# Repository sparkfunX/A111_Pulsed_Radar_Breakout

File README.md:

SparkX A111 Pulsed Radar Breakout
========================================

[*SparkX  A111 Pulsed Radar Breakout (SPX-14811)*](https://www.sparkfun.com/products/14811)

Does your project require high-precision, cutting-edge distance measurement? Or maybe speed-, motion-, or gesture-sensing? We’re not talking about simple ultrasonic, or even infrared, sensors here, but 60GHz radar! Well say hello to our tiny, pulsed-radar friend: the Acconeer A111.

The A111 is a single-chip solution for pulsed coherent radar (PCR). It comes complete with integrated antennae and an SPI interface capable of clock speeds of up to 50MHz. The A111’s primary use case is distance-sensing, but it also supports applications in gesture-, motion-, material-, and speed-detection. It can see objects at distances of up to two meters.

Our breakout board for the A111 includes a 1.8V regulator, voltage-level translation between 1.8V and either 3.3V or 5V, and, of course, it breaks out all pins of the pulsed radar sensor to both 0.1-inch and Raspberry Pi-friendly headers.

The breakout board is primarily **designed to interface directly with a Raspberry Pi** – Acconeer’s SDK currently only supports ARMv7’s (e.g. a Pi) and ARM Cortex-M4’s. Check out our <a href="https://learn.sparkfun.com/tutorials/using-the-a111-pulsed-radar-sensor-with-a-raspberry-pi">Using the A111 Pulsed Radar Breakout tutorial</a>, which explains how to use the sensor with a Raspberry Pi.

**Update!**
The tutorial describes the process for an older version of the
Acconeer SDK that is nolonger available.

New installation instructions:
1. Download and unpack Acconeer SDK 1.7.0 for XC111
2. Copy the `user_source` and `user_rule` folders from this repository to the root of the unpacked
   SDK (folders `lib`, `source` and `rule` should be siblings to the
   `user_rule`and `user_source`)

SparkFun labored with love to create this code. Feel like supporting open source hardware? 
Buy a [breakout board](https://www.sparkfun.com/products/14811) from SparkFun!

Repository Contents
-------------------

* **/Documents** - Datasheets
* **/Hardware** - Eagle design files (.brd, .sch)
* **/Software** - Example code and board-definition files to be added to the Acconeer ARMv7 SDK

License Information
-------------------

This product is _**open source**_! 

If you have any questions or concerns on licensing, please contact techsupport@sparkfun.com.

Please use, reuse, and modify these files as you see fit. Please maintain attribution to SparkFun Electronics and release any derivative under the same license.

Distributed as-is; no warranty is given.

- Your friends at SparkFun.

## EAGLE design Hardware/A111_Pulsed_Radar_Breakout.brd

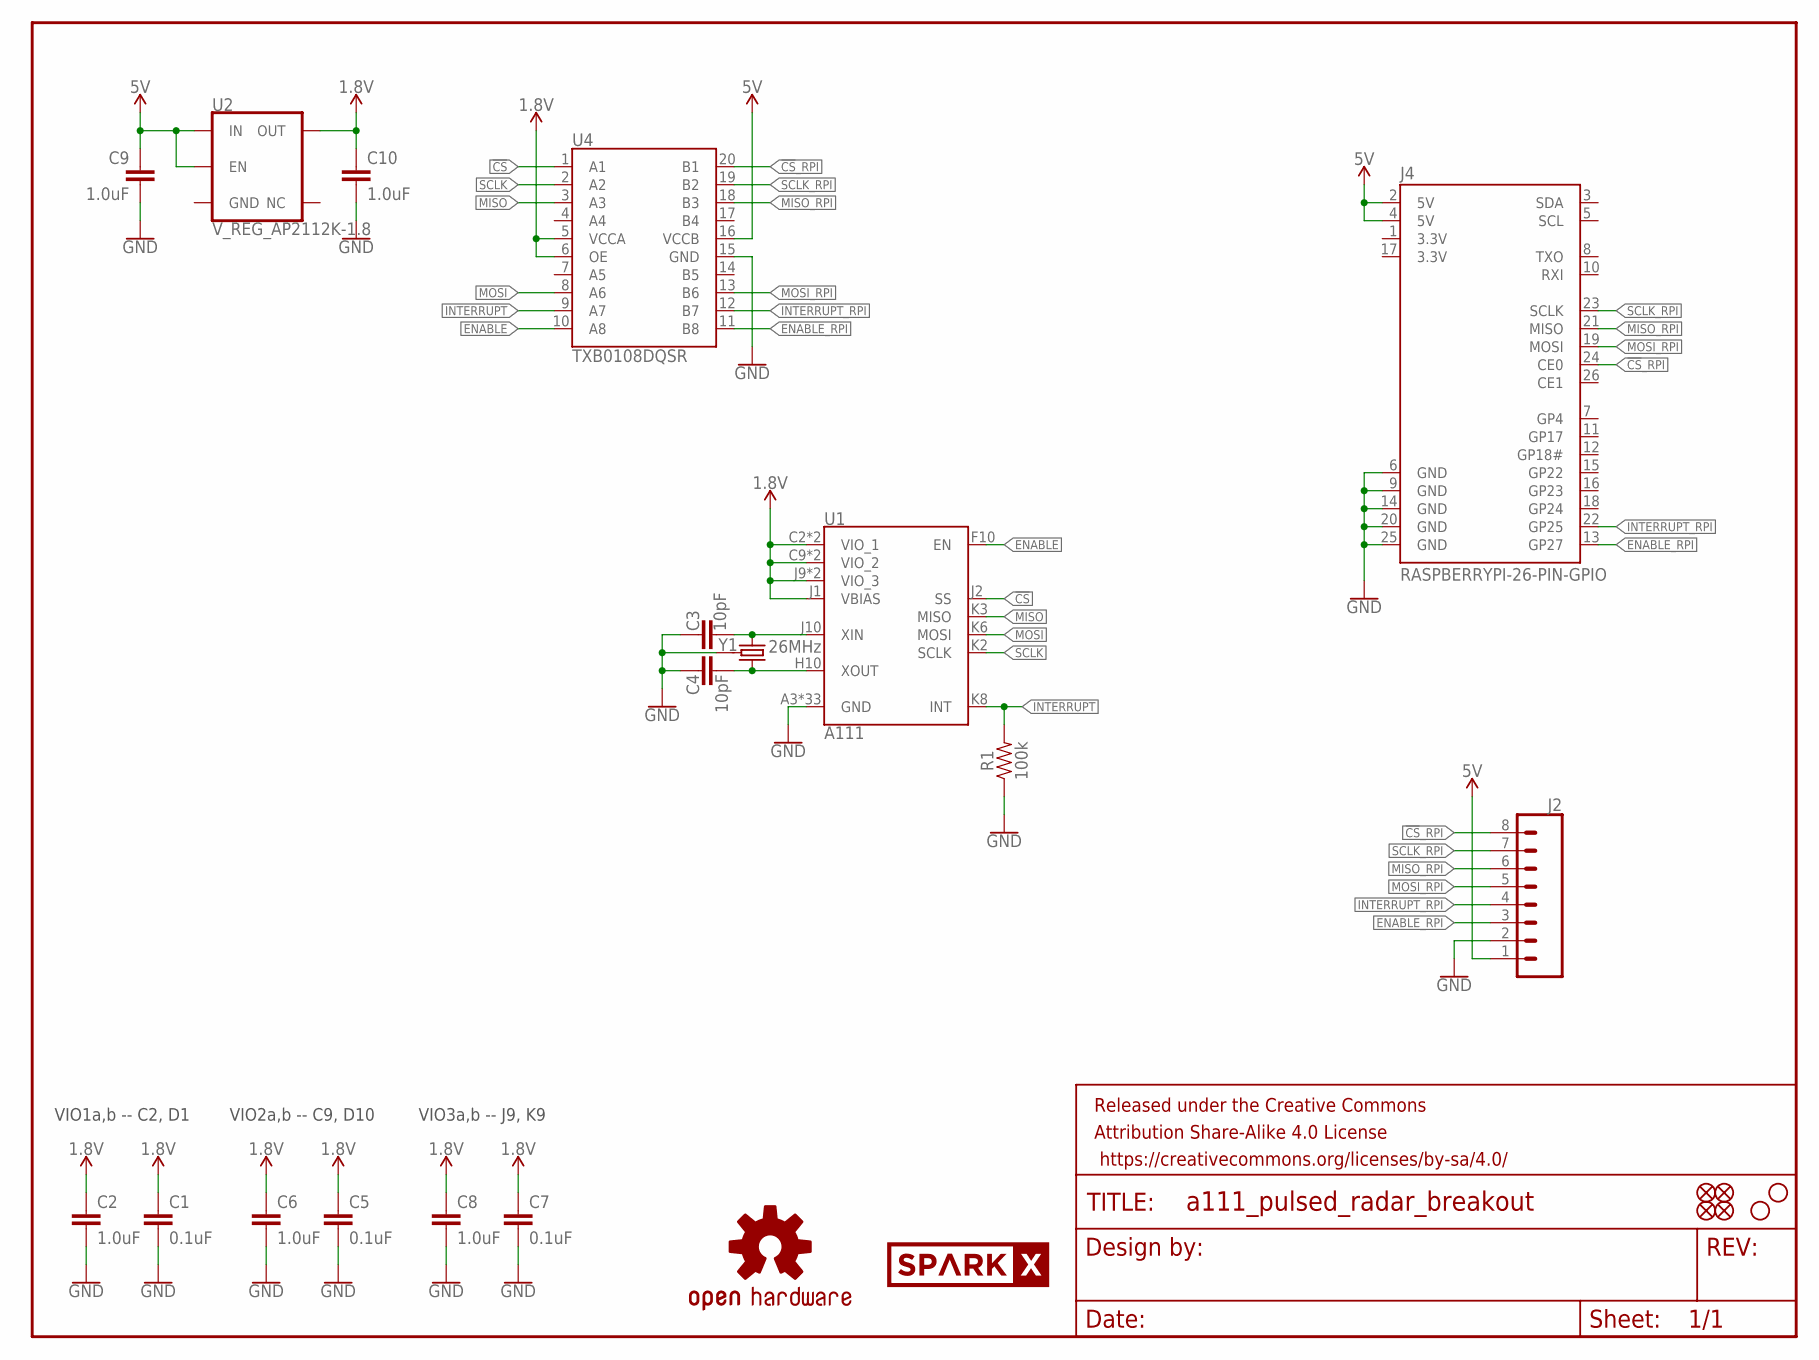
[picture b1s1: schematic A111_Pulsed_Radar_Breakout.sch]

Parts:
C1, C5, C7: 0.1uF; 0603
C2, C6, C8, C9, C10: 1.0uF; 0603
C3, C4: 10pF; 0603
FD1, FD2, FD3, FD4: FIDUCIALUFIDUCIAL; FIDUCIAL-MICRO
FRAME1: FRAME-LETTER; CREATIVE_COMMONS
H1, H2: STAND-OFF
J2: CONN_08NO_SILK_FEMALE_PTH; 1X08_NO_SILK
J4: RASPBERRYPI-26-PIN-GPIO; 2X13
LOGO1: SPARKX-LOGO5; SPARKX-LARGE
LOGO2: OSHW-LOGOM; OSHW-LOGO-M
R1: 100k; 0603
U1: A111
U2: V_REG_AP2112K-1.8; SOT23-5
U4: TXB0108DQSR; UFDFN-20
Y1: 26MHz; CRYSTAL-SMD-3.2X2.5MM

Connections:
1.8V: C1.1, C2.1, C5.1, C6.1, C7.1, C8.1, C10.1, U1.C2 (VIO_1), U1.C9 (VIO_2), U1.D1 (VIO_1), U1.D10 (VIO_2), U1.J1 (VBIAS), U1.J9 (VIO_3), U1.K9 (VIO_3), U2.5 (OUT), U4.5 (VCCA), U4.6 (OE)
5V: C9.1, J2.1, J4.2 (5V), J4.4 (5V), U2.1 (IN), U2.3 (EN), U4.16 (VCCB)
!CS!: U1.J2 (SS), U4.1 (A1)
!CS!_RPI: J2.8, J4.24 (CE0), U4.20 (B1)
ENABLE: U1.F10 (EN), U4.10 (A8)
ENABLE_RPI: J2.3, J4.13 (GP27), U4.11 (B8)
GND: C1.2, C2.2, C3.2, C4.1, C5.2, C6.2, C7.2, C8.2, C9.2, C10.2, J2.2, J4.6 (GND), J4.9 (GND), J4.14 (GND), J4.20 (GND), J4.25 (GND), R1.1, U1.A3 (GND), U1.A4 (GND), U1.A5 (GND), U1.A6 (GND), U1.A7 (GND), U1.A8 (GND), U1.A9 (GND), U1.B2 (GND), U1.B9 (GND), U1.B10 (GND), U1.C1 (GND), U1.C10 (GND), U1.D2 (GND), U1.D9 (GND), U1.E1 (GND), U1.E2 (GND), U1.E9 (GND), U1.E10 (GND), U1.F1 (GND), U1.F2 (GND), U1.F9 (GND), U1.G1 (GND), U1.G10 (GND), U1.H1 (GND), U1.H2 (GND), U1.H9 (GND), U1.J3 (GND), U1.J5 (GND), U1.J6 (GND), U1.J8 (GND), U1.K4 (GND), U1.K5 (GND), U1.K7 (GND), U4.15 (GND), Y1.2 (3), Y1.4 (3)
INTERRUPT: R1.2, U1.K8 (INT), U4.9 (A7)
INTERRUPT_RPI: J2.4, J4.22 (GP25), U4.12 (B7)
MISO: U1.K3 (MISO), U4.3 (A3)
MISO_RPI: J2.6, J4.21 (MISO), U4.18 (B3)
MOSI: U1.K6 (MOSI), U4.8 (A6)
MOSI_RPI: J2.5, J4.19 (MOSI), U4.13 (B6)
unnamed: C3.1, U1.J10 (XIN), Y1.1
unnamed: C4.2, U1.H10 (XOUT), Y1.3 (2)
SCLK: U1.K2 (SCLK), U4.2 (A2)
SCLK_RPI: J2.7, J4.23 (SCLK), U4.19 (B2)

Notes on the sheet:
VIO1a,b -- C2, D1
VIO2a,b -- C9, D10
VIO3a,b -- J9, K9

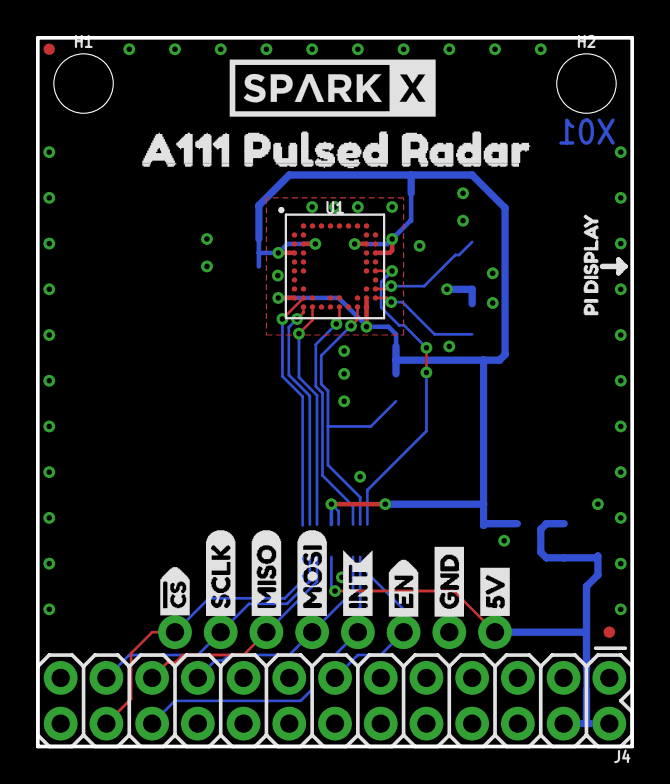
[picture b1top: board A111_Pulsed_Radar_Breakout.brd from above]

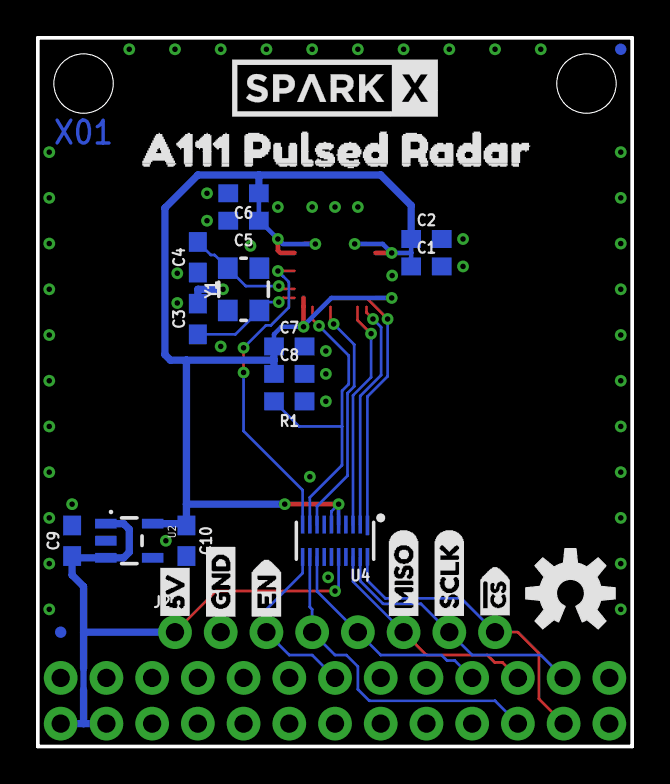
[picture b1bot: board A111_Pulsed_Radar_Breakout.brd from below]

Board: 2 copper layers, 33.0 x 39.4 mm, 44 parts (26 on the bottom side), 17 nets.

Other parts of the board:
LOGO3: SPARKX-LOGO5; SPARKX-LARGE
U$1, U$9: A111_PULSED_RADAR9
U$2, U$10: SCLK3
U$3, U$11: MISO4
U$4: MOSI5
U$5: INT8
U$6, U$18: EN9
U$7, U$15: GND0
U$8, U$16: 5V1
U$12: PI_DISPLAY9
U$13, U$17: #CS9

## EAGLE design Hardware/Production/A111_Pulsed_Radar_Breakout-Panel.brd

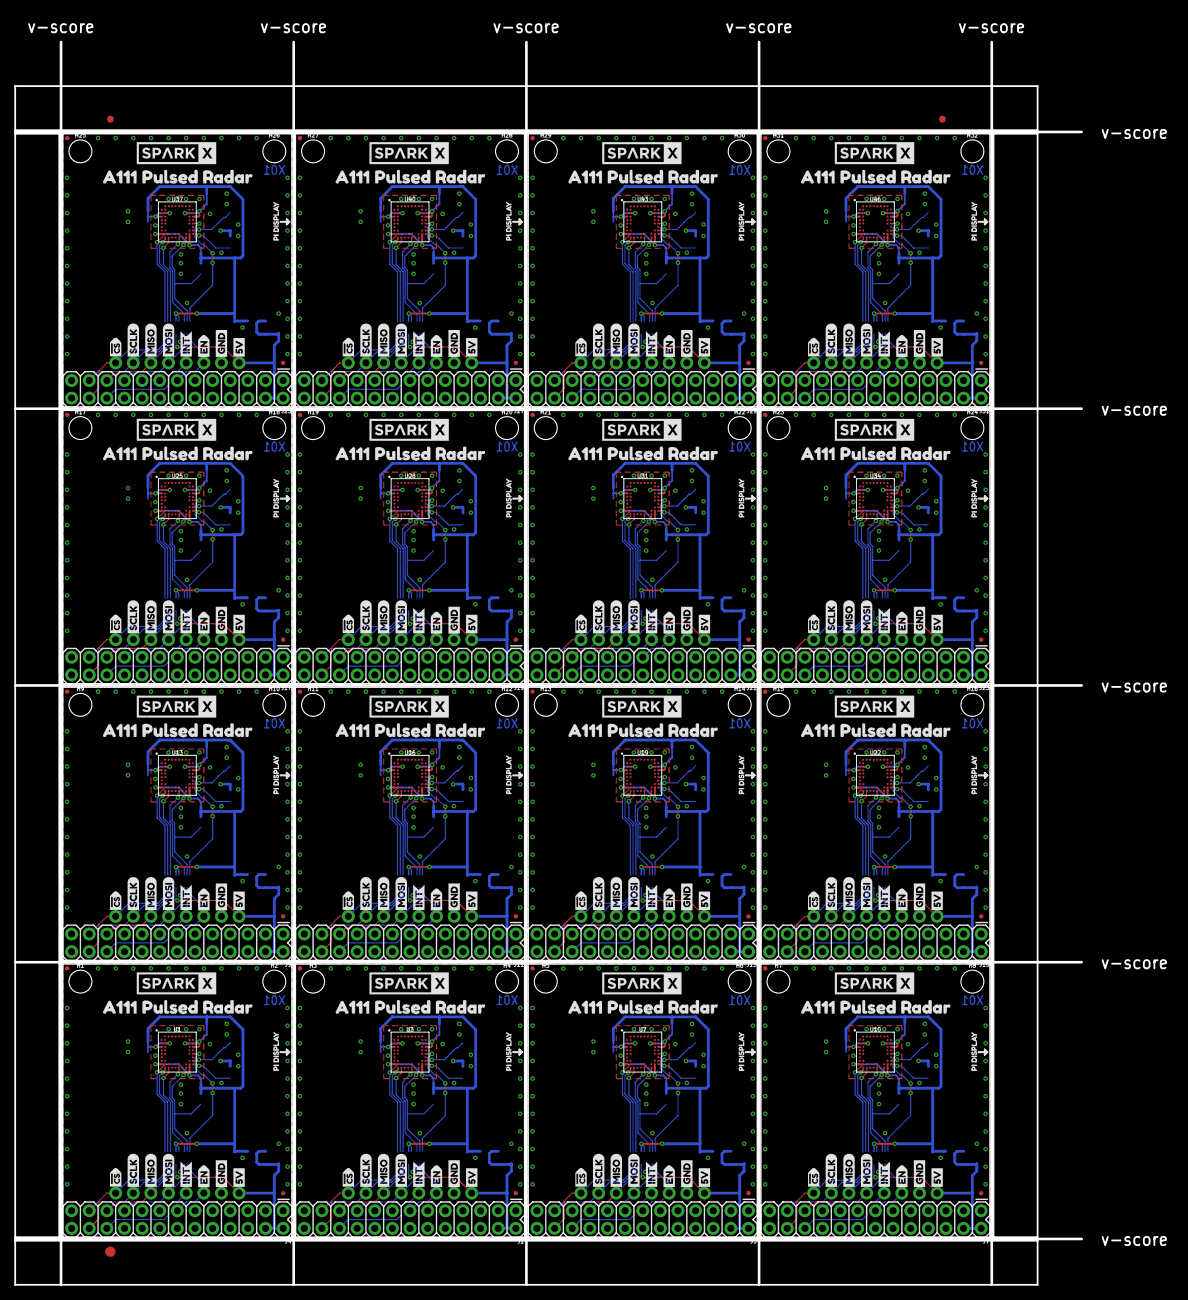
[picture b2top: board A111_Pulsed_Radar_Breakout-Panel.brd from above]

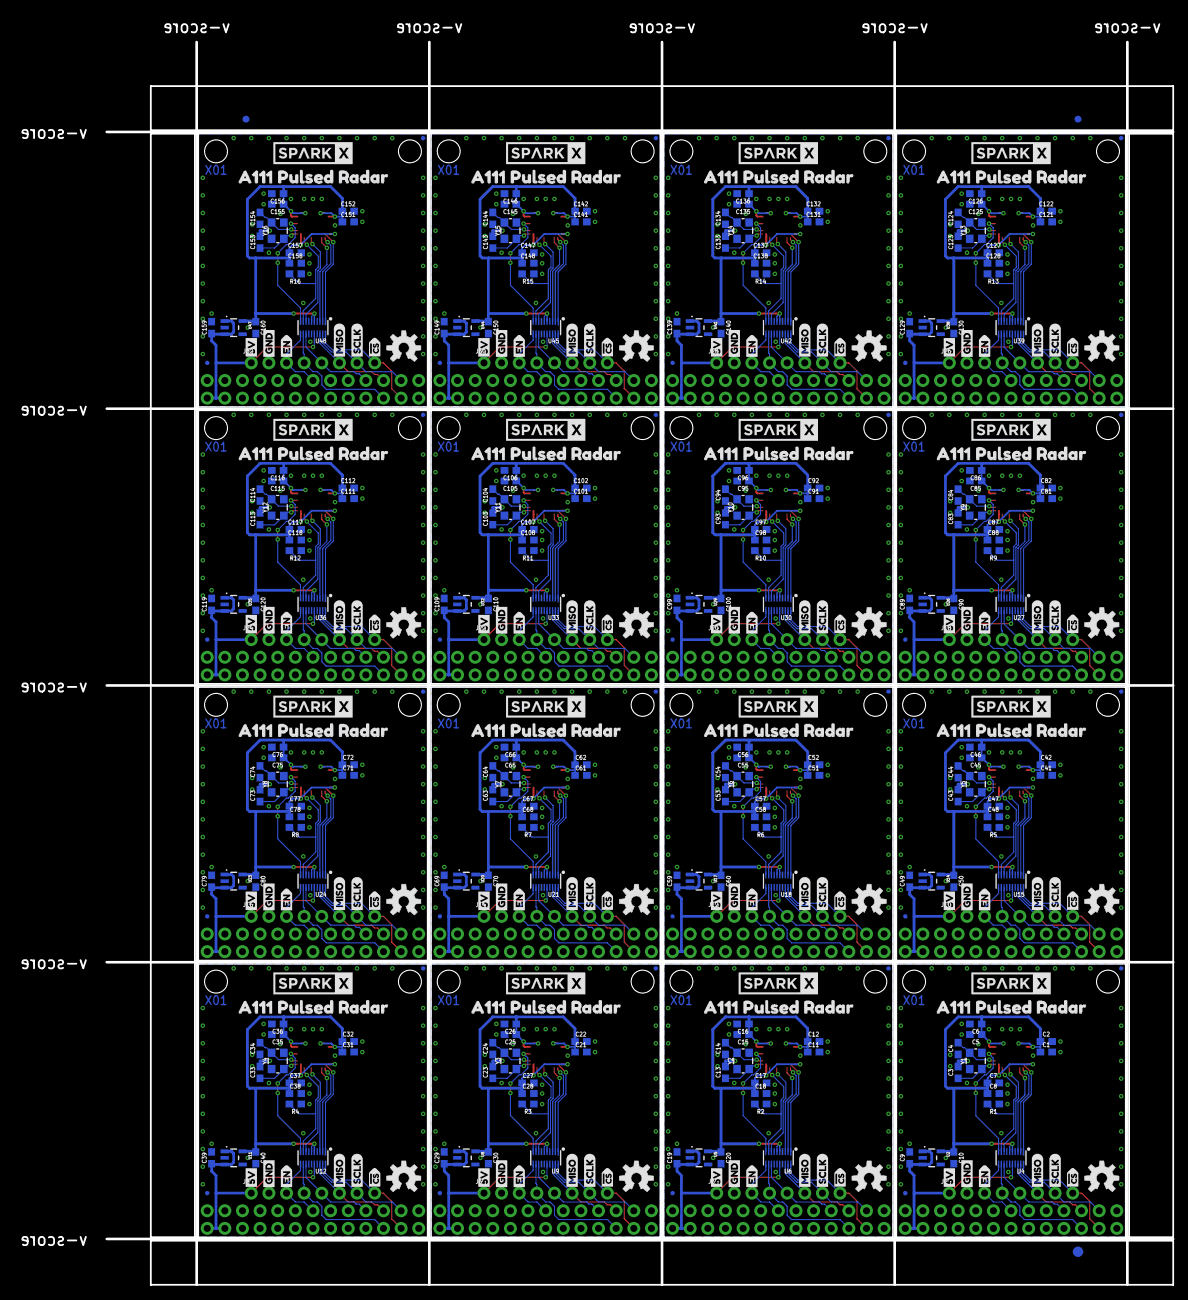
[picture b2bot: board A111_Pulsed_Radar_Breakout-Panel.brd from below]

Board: 2 copper layers, 166.9 x 182.9 mm, 694 parts (419 on the bottom side), 272 nets.

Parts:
C1, C5, C7, C11, C15, C17, C21, C25, C27, C31, C35, C37, C41, C45, C47, C51, C55, C57, C61, C65, C67, C71, C75, C77, C81, C85, C87, C91, C95, C97, C101, C105, C107, C111, C115, C117, C121, C125, C127, C131, C135, C137, C141, C145, C147, C151, C155, C157: 0.1uF; 0603
C2, C6, C8, C9, C10, C12, C16, C18, C19, C20, C22, C26, C28, C29, C30, C32, C36, C38, C39, C40, C42, C46, C48, C49, C50, C52, C56, C58, C59, C60, C62, C66, C68, C69, C70, C72, C76, C78, C79, C80, C82, C86, C88, C89, C90, C92, C96, C98, C99, C100, C102, C106, C108, C109, C110, C112, C116, C118, C119, C120, C122, C126, C128, C129, C130, C132, C136, C138, C139, C140, C142, C146, C148, C149, C150, C152, C156, C158, C159, C160: 1.0uF; 0603
C3, C4, C13, C14, C23, C24, C33, C34, C43, C44, C53, C54, C63, C64, C73, C74, C83, C84, C93, C94, C103, C104, C113, C114, C123, C124, C133, C134, C143, C144, C153, C154: 10pF; 0603
E$1, E$2, E$3, E$4: FIDUCIAL-1X2
E$5, E$6: FIDUCIAL-1.5X3
FD1, FD2, FD3, FD4, FD5, FD6, FD7, FD8, FD9, FD10, FD11, FD12, FD13, FD14, FD15, FD16, FD17, FD18, FD19, FD20, FD21, FD22, FD23, FD24, FD25, FD26, FD27, FD28, FD29, FD30, FD31, FD32, FD33, FD34, FD35, FD36, FD37, FD38, FD39, FD40, FD41, FD42, FD43, FD44, FD45, FD46, FD47, FD48, FD49, FD50, FD51, FD52, FD53, FD54, FD55, FD56, FD57, FD58, FD59, FD60, FD61, FD62, FD63, FD64: FIDUCIALUFIDUCIAL; FIDUCIAL-MICRO
H1, H2, H3, H4, H5, H6, H7, H8, H9, H10, H11, H12, H13, H14, H15, H16, H17, H18, H19, H20, H21, H22, H23, H24, H25, H26, H27, H28, H29, H30, H31, H32: STAND-OFF
J1, J4, J5, J7, J9, J11, J13, J15, J17, J19, J21, J23, J25, J27, J29, J31: RASPBERRYPI-26-PIN-GPIO; 2X13
J2, J3, J6, J8, J10, J12, J14, J16, J18, J20, J22, J24, J26, J28, J30, J32: 1X08_NO_SILK
LOGO1, LOGO3, LOGO4, LOGO6, LOGO7, LOGO9, LOGO10, LOGO12, LOGO13, LOGO15, LOGO16, LOGO18, LOGO19, LOGO21, LOGO22, LOGO24, LOGO25, LOGO27, LOGO28, LOGO30, LOGO31, LOGO33, LOGO34, LOGO36, LOGO37, LOGO39, LOGO40, LOGO42, LOGO43, LOGO45, LOGO46, LOGO48: SPARKX-LOGO5; SPARKX-LARGE
LOGO2, LOGO5, LOGO8, LOGO11, LOGO14, LOGO17, LOGO20, LOGO23, LOGO26, LOGO29, LOGO32, LOGO35, LOGO38, LOGO41, LOGO44, LOGO47: OSHW-LOGOM; OSHW-LOGO-M
R1, R2, R3, R4, R5, R6, R7, R8, R9, R10, R11, R12, R13, R14, R15, R16: 100k; 0603
U1, U3, U7, U10, U13, U16, U19, U22, U25, U28, U31, U34, U37, U40, U43, U46: A111
U2, U5, U8, U11, U14, U17, U20, U23, U26, U29, U32, U35, U38, U41, U44, U47: V_REG_AP2112K-1.8; SOT23-5
U4, U6, U9, U12, U15, U18, U21, U24, U27, U30, U33, U36, U39, U42, U45, U48: TXB0108DQSR; UFDFN-20
U$1, U$9, U$29, U$30, U$46, U$47, U$63, U$64, U$80, U$81, U$97, U$98, U$114, U$115, U$131, U$132, U$148, U$149, U$165, U$166, U$182, U$183, U$199, U$200, U$216, U$217, U$233, U$234, U$250, U$251, U$267, U$268: A111_PULSED_RADAR9
U$2, U$10, U$14, U$24, U$35, U$41, U$52, U$58, U$69, U$75, U$86, U$92, U$103, U$109, U$120, U$126, U$137, U$143, U$154, U$160, U$171, U$177, U$188, U$194, U$205, U$211, U$222, U$228, U$239, U$245, U$256, U$262: SCLK3
U$3, U$11, U$19, U$25, U$36, U$42, U$53, U$59, U$70, U$76, U$87, U$93, U$104, U$110, U$121, U$127, U$138, U$144, U$155, U$161, U$172, U$178, U$189, U$195, U$206, U$212, U$223, U$229, U$240, U$246, U$257, U$263: MISO4
U$4, U$20, U$37, U$54, U$71, U$88, U$105, U$122, U$139, U$156, U$173, U$190, U$207, U$224, U$241, U$258: MOSI5
U$5, U$21, U$38, U$55, U$72, U$89, U$106, U$123, U$140, U$157, U$174, U$191, U$208, U$225, U$242, U$259: INT8
U$6, U$18, U$33, U$34, U$50, U$51, U$67, U$68, U$84, U$85, U$101, U$102, U$118, U$119, U$135, U$136, U$152, U$153, U$169, U$170, U$186, U$187, U$203, U$204, U$220, U$221, U$237, U$238, U$254, U$255, U$271, U$272: EN9
U$7, U$15, U$22, U$26, U$39, U$43, U$56, U$60, U$73, U$77, U$90, U$94, U$107, U$111, U$124, U$128, U$141, U$145, U$158, U$162, U$175, U$179, U$192, U$196, U$209, U$213, U$226, U$230, U$243, U$247, U$260, U$264: GND0
U$8, U$16, U$23, U$27, U$40, U$44, U$57, U$61, U$74, U$78, U$91, U$95, U$108, U$112, U$125, U$129, U$142, U$146, U$159, U$163, U$176, U$180, U$193, U$197, U$210, U$214, U$227, U$231, U$244, U$248, U$261, U$265: 5V1
U$12, U$31, U$48, U$65, U$82, U$99, U$116, U$133, U$150, U$167, U$184, U$201, U$218, U$235, U$252, U$269: PI_DISPLAY9
U$13, U$17, U$28, U$32, U$45, U$49, U$62, U$66, U$79, U$83, U$96, U$100, U$113, U$117, U$130, U$134, U$147, U$151, U$164, U$168, U$181, U$185, U$198, U$202, U$215, U$219, U$232, U$236, U$249, U$253, U$266, U$270: #CS9
Y1, Y2, Y3, Y4, Y5, Y6, Y7, Y8, Y9, Y10, Y11, Y12, Y13, Y14, Y15, Y16: 26MHz; CRYSTAL-SMD-3.2X2.5MM

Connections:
1.8V: C1.1, C2.1, C5.1, C6.1, C7.1, C8.1, C10.1, U1.C2, U1.C9, U1.D1, U1.D10, U1.J1, U1.J9, U1.K9, U2.5, U4.5, U4.6
1.8V1: C11.1, C12.1, C15.1, C16.1, C17.1, C18.1, C20.1, U3.C2, U3.C9, U3.D1, U3.D10, U3.J1, U3.J9, U3.K9, U5.5, U6.5, U6.6
1.8V2: C21.1, C22.1, C25.1, C26.1, C27.1, C28.1, C30.1, U7.C2, U7.C9, U7.D1, U7.D10, U7.J1, U7.J9, U7.K9, U8.5, U9.5, U9.6
1.8V3: C31.1, C32.1, C35.1, C36.1, C37.1, C38.1, C40.1, U10.C2, U10.C9, U10.D1, U10.D10, U10.J1, U10.J9, U10.K9, U11.5, U12.5, U12.6
1.8V4: C41.1, C42.1, C45.1, C46.1, C47.1, C48.1, C50.1, U13.C2, U13.C9, U13.D1, U13.D10, U13.J1, U13.J9, U13.K9, U14.5, U15.5, U15.6
1.8V5: C51.1, C52.1, C55.1, C56.1, C57.1, C58.1, C60.1, U16.C2, U16.C9, U16.D1, U16.D10, U16.J1, U16.J9, U16.K9, U17.5, U18.5, U18.6
1.8V6: C61.1, C62.1, C65.1, C66.1, C67.1, C68.1, C70.1, U19.C2, U19.C9, U19.D1, U19.D10, U19.J1, U19.J9, U19.K9, U20.5, U21.5, U21.6
1.8V7: C71.1, C72.1, C75.1, C76.1, C77.1, C78.1, C80.1, U22.C2, U22.C9, U22.D1, U22.D10, U22.J1, U22.J9, U22.K9, U23.5, U24.5, U24.6
1.8V8: C81.1, C82.1, C85.1, C86.1, C87.1, C88.1, C90.1, U25.C2, U25.C9, U25.D1, U25.D10, U25.J1, U25.J9, U25.K9, U26.5, U27.5, U27.6
1.8V9: C91.1, C92.1, C95.1, C96.1, C97.1, C98.1, C100.1, U28.C2, U28.C9, U28.D1, U28.D10, U28.J1, U28.J9, U28.K9, U29.5, U30.5, U30.6
1.8V10: C101.1, C102.1, C105.1, C106.1, C107.1, C108.1, C110.1, U31.C2, U31.C9, U31.D1, U31.D10, U31.J1, U31.J9, U31.K9, U32.5, U33.5, U33.6
1.8V11: C111.1, C112.1, C115.1, C116.1, C117.1, C118.1, C120.1, U34.C2, U34.C9, U34.D1, U34.D10, U34.J1, U34.J9, U34.K9, U35.5, U36.5, U36.6
1.8V12: C121.1, C122.1, C125.1, C126.1, C127.1, C128.1, C130.1, U37.C2, U37.C9, U37.D1, U37.D10, U37.J1, U37.J9, U37.K9, U38.5, U39.5, U39.6
1.8V13: C131.1, C132.1, C135.1, C136.1, C137.1, C138.1, C140.1, U40.C2, U40.C9, U40.D1, U40.D10, U40.J1, U40.J9, U40.K9, U41.5, U42.5, U42.6
1.8V14: C141.1, C142.1, C145.1, C146.1, C147.1, C148.1, C150.1, U43.C2, U43.C9, U43.D1, U43.D10, U43.J1, U43.J9, U43.K9, U44.5, U45.5, U45.6
1.8V15: C151.1, C152.1, C155.1, C156.1, C157.1, C158.1, C160.1, U46.C2, U46.C9, U46.D1, U46.D10, U46.J1, U46.J9, U46.K9, U47.5, U48.5, U48.6
5V: C9.1, J2.1, J4.2, J4.4, U2.1, U2.3, U4.16
5V1: C19.1, J1.2, J1.4, J3.1, U5.1, U5.3, U6.16
5V2: C29.1, J5.2, J5.4, J6.1, U8.1, U8.3, U9.16
5V3: C39.1, J7.2, J7.4, J8.1, U11.1, U11.3, U12.16
5V4: C49.1, J9.2, J9.4, J10.1, U14.1, U14.3, U15.16
5V5: C59.1, J11.2, J11.4, J12.1, U17.1, U17.3, U18.16
5V6: C69.1, J13.2, J13.4, J14.1, U20.1, U20.3, U21.16
5V7: C79.1, J15.2, J15.4, J16.1, U23.1, U23.3, U24.16
5V8: C89.1, J17.2, J17.4, J18.1, U26.1, U26.3, U27.16
5V9: C99.1, J19.2, J19.4, J20.1, U29.1, U29.3, U30.16
5V10: C109.1, J21.2, J21.4, J22.1, U32.1, U32.3, U33.16
5V11: C119.1, J23.2, J23.4, J24.1, U35.1, U35.3, U36.16
5V12: C129.1, J25.2, J25.4, J26.1, U38.1, U38.3, U39.16
5V13: C139.1, J27.2, J27.4, J28.1, U41.1, U41.3, U42.16
5V14: C149.1, J29.2, J29.4, J30.1, U44.1, U44.3, U45.16
5V15: C159.1, J31.2, J31.4, J32.1, U47.1, U47.3, U48.16
!CS!: U1.J2, U4.1
!CS!1: U3.J2, U6.1
!CS!2: U7.J2, U9.1
!CS!3: U10.J2, U12.1
!CS!4: U13.J2, U15.1
!CS!5: U16.J2, U18.1
!CS!6: U19.J2, U21.1
!CS!7: U22.J2, U24.1
!CS!8: U25.J2, U27.1
!CS!9: U28.J2, U30.1
!CS!10: U31.J2, U33.1
!CS!11: U34.J2, U36.1
!CS!12: U37.J2, U39.1
!CS!13: U40.J2, U42.1
!CS!14: U43.J2, U45.1
!CS!15: U46.J2, U48.1
!CS!_RPI: J2.8, J4.24, U4.20
!CS!_RPI1: J1.24, J3.8, U6.20
!CS!_RPI2: J5.24, J6.8, U9.20
!CS!_RPI3: J7.24, J8.8, U12.20
!CS!_RPI4: J9.24, J10.8, U15.20
!CS!_RPI5: J11.24, J12.8, U18.20
!CS!_RPI6: J13.24, J14.8, U21.20
!CS!_RPI7: J15.24, J16.8, U24.20
!CS!_RPI8: J17.24, J18.8, U27.20
!CS!_RPI9: J19.24, J20.8, U30.20
!CS!_RPI10: J21.24, J22.8, U33.20
!CS!_RPI11: J23.24, J24.8, U36.20
!CS!_RPI12: J25.24, J26.8, U39.20
!CS!_RPI13: J27.24, J28.8, U42.20
!CS!_RPI14: J29.24, J30.8, U45.20
!CS!_RPI15: J31.24, J32.8, U48.20
ENABLE: U1.F10, U4.10
ENABLE1: U3.F10, U6.10
ENABLE2: U7.F10, U9.10
ENABLE3: U10.F10, U12.10
ENABLE4: U13.F10, U15.10
ENABLE5: U16.F10, U18.10
ENABLE6: U19.F10, U21.10
ENABLE7: U22.F10, U24.10
ENABLE8: U25.F10, U27.10
ENABLE9: U28.F10, U30.10
ENABLE10: U31.F10, U33.10
ENABLE11: U34.F10, U36.10
ENABLE12: U37.F10, U39.10
ENABLE13: U40.F10, U42.10
ENABLE14: U43.F10, U45.10
ENABLE15: U46.F10, U48.10
ENABLE_RPI: J2.3, J4.13, U4.11
ENABLE_RPI1: J1.13, J3.3, U6.11
ENABLE_RPI2: J5.13, J6.3, U9.11
ENABLE_RPI3: J7.13, J8.3, U12.11
ENABLE_RPI4: J9.13, J10.3, U15.11
ENABLE_RPI5: J11.13, J12.3, U18.11
ENABLE_RPI6: J13.13, J14.3, U21.11
ENABLE_RPI7: J15.13, J16.3, U24.11
ENABLE_RPI8: J17.13, J18.3, U27.11
ENABLE_RPI9: J19.13, J20.3, U30.11
ENABLE_RPI10: J21.13, J22.3, U33.11
ENABLE_RPI11: J23.13, J24.3, U36.11
ENABLE_RPI12: J25.13, J26.3, U39.11
ENABLE_RPI13: J27.13, J28.3, U42.11
ENABLE_RPI14: J29.13, J30.3, U45.11
ENABLE_RPI15: J31.13, J32.3, U48.11
GND: C1.2, C2.2, C3.2, C4.1, C5.2, C6.2, C7.2, C8.2, C9.2, C10.2, J2.2, J4.6, J4.9, J4.14, J4.20, J4.25, R1.1, U1.A3, U1.A4, U1.A5, U1.A6, U1.A7, U1.A8, U1.A9, U1.B2, U1.B9, U1.B10, U1.C1, U1.C10, U1.D2, U1.D9, U1.E1, U1.E2, U1.E9, U1.E10, U1.F1, U1.F2, U1.F9, U1.G1, U1.G10, U1.H1, U1.H2, U1.H9, U1.J3, U1.J5, U1.J6, U1.J8, U1.K4, U1.K5, U1.K7, U4.15, Y1.2, Y1.4
GND1: C11.2, C12.2, C13.2, C14.1, C15.2, C16.2, C17.2, C18.2, C19.2, C20.2, J1.6, J1.9, J1.14, J1.20, J1.25, J3.2, R2.1, U3.A3, U3.A4, U3.A5, U3.A6, U3.A7, U3.A8, U3.A9, U3.B2, U3.B9, U3.B10, U3.C1, U3.C10, U3.D2, U3.D9, U3.E1, U3.E2, U3.E9, U3.E10, U3.F1, U3.F2, U3.F9, U3.G1, U3.G10, U3.H1, U3.H2, U3.H9, U3.J3, U3.J5, U3.J6, U3.J8, U3.K4, U3.K5, U3.K7, U6.15, Y2.2, Y2.4
GND2: C21.2, C22.2, C23.2, C24.1, C25.2, C26.2, C27.2, C28.2, C29.2, C30.2, J5.6, J5.9, J5.14, J5.20, J5.25, J6.2, R3.1, U7.A3, U7.A4, U7.A5, U7.A6, U7.A7, U7.A8, U7.A9, U7.B2, U7.B9, U7.B10, U7.C1, U7.C10, U7.D2, U7.D9, U7.E1, U7.E2, U7.E9, U7.E10, U7.F1, U7.F2, U7.F9, U7.G1, U7.G10, U7.H1, U7.H2, U7.H9, U7.J3, U7.J5, U7.J6, U7.J8, U7.K4, U7.K5, U7.K7, U9.15, Y3.2, Y3.4
GND3: C31.2, C32.2, C33.2, C34.1, C35.2, C36.2, C37.2, C38.2, C39.2, C40.2, J7.6, J7.9, J7.14, J7.20, J7.25, J8.2, R4.1, U10.A3, U10.A4, U10.A5, U10.A6, U10.A7, U10.A8, U10.A9, U10.B2, U10.B9, U10.B10, U10.C1, U10.C10, U10.D2, U10.D9, U10.E1, U10.E2, U10.E9, U10.E10, U10.F1, U10.F2, U10.F9, U10.G1, U10.G10, U10.H1, U10.H2, U10.H9, U10.J3, U10.J5, U10.J6, U10.J8, U10.K4, U10.K5, U10.K7, U12.15, Y4.2, Y4.4
GND4: C41.2, C42.2, C43.2, C44.1, C45.2, C46.2, C47.2, C48.2, C49.2, C50.2, J9.6, J9.9, J9.14, J9.20, J9.25, J10.2, R5.1, U13.A3, U13.A4, U13.A5, U13.A6, U13.A7, U13.A8, U13.A9, U13.B2, U13.B9, U13.B10, U13.C1, U13.C10, U13.D2, U13.D9, U13.E1, U13.E2, U13.E9, U13.E10, U13.F1, U13.F2, U13.F9, U13.G1, U13.G10, U13.H1, U13.H2, U13.H9, U13.J3, U13.J5, U13.J6, U13.J8, U13.K4, U13.K5, U13.K7, U15.15, Y5.2, Y5.4
GND5: C51.2, C52.2, C53.2, C54.1, C55.2, C56.2, C57.2, C58.2, C59.2, C60.2, J11.6, J11.9, J11.14, J11.20, J11.25, J12.2, R6.1, U16.A3, U16.A4, U16.A5, U16.A6, U16.A7, U16.A8, U16.A9, U16.B2, U16.B9, U16.B10, U16.C1, U16.C10, U16.D2, U16.D9, U16.E1, U16.E2, U16.E9, U16.E10, U16.F1, U16.F2, U16.F9, U16.G1, U16.G10, U16.H1, U16.H2, U16.H9, U16.J3, U16.J5, U16.J6, U16.J8, U16.K4, U16.K5, U16.K7, U18.15, Y6.2, Y6.4
GND6: C61.2, C62.2, C63.2, C64.1, C65.2, C66.2, C67.2, C68.2, C69.2, C70.2, J13.6, J13.9, J13.14, J13.20, J13.25, J14.2, R7.1, U19.A3, U19.A4, U19.A5, U19.A6, U19.A7, U19.A8, U19.A9, U19.B2, U19.B9, U19.B10, U19.C1, U19.C10, U19.D2, U19.D9, U19.E1, U19.E2, U19.E9, U19.E10, U19.F1, U19.F2, U19.F9, U19.G1, U19.G10, U19.H1, U19.H2, U19.H9, U19.J3, U19.J5, U19.J6, U19.J8, U19.K4, U19.K5, U19.K7, U21.15, Y7.2, Y7.4
GND7: C71.2, C72.2, C73.2, C74.1, C75.2, C76.2, C77.2, C78.2, C79.2, C80.2, J15.6, J15.9, J15.14, J15.20, J15.25, J16.2, R8.1, U22.A3, U22.A4, U22.A5, U22.A6, U22.A7, U22.A8, U22.A9, U22.B2, U22.B9, U22.B10, U22.C1, U22.C10, U22.D2, U22.D9, U22.E1, U22.E2, U22.E9, U22.E10, U22.F1, U22.F2, U22.F9, U22.G1, U22.G10, U22.H1, U22.H2, U22.H9, U22.J3, U22.J5, U22.J6, U22.J8, U22.K4, U22.K5, U22.K7, U24.15, Y8.2, Y8.4
GND8: C81.2, C82.2, C83.2, C84.1, C85.2, C86.2, C87.2, C88.2, C89.2, C90.2, J17.6, J17.9, J17.14, J17.20, J17.25, J18.2, R9.1, U25.A3, U25.A4, U25.A5, U25.A6, U25.A7, U25.A8, U25.A9, U25.B2, U25.B9, U25.B10, U25.C1, U25.C10, U25.D2, U25.D9, U25.E1, U25.E2, U25.E9, U25.E10, U25.F1, U25.F2, U25.F9, U25.G1, U25.G10, U25.H1, U25.H2, U25.H9, U25.J3, U25.J5, U25.J6, U25.J8, U25.K4, U25.K5, U25.K7, U27.15, Y9.2, Y9.4
GND9: C91.2, C92.2, C93.2, C94.1, C95.2, C96.2, C97.2, C98.2, C99.2, C100.2, J19.6, J19.9, J19.14, J19.20, J19.25, J20.2, R10.1, U28.A3, U28.A4, U28.A5, U28.A6, U28.A7, U28.A8, U28.A9, U28.B2, U28.B9, U28.B10, U28.C1, U28.C10, U28.D2, U28.D9, U28.E1, U28.E2, U28.E9, U28.E10, U28.F1, U28.F2, U28.F9, U28.G1, U28.G10, U28.H1, U28.H2, U28.H9, U28.J3, U28.J5, U28.J6, U28.J8, U28.K4, U28.K5, U28.K7, U30.15, Y10.2, Y10.4
GND10: C101.2, C102.2, C103.2, C104.1, C105.2, C106.2, C107.2, C108.2, C109.2, C110.2, J21.6, J21.9, J21.14, J21.20, J21.25, J22.2, R11.1, U31.A3, U31.A4, U31.A5, U31.A6, U31.A7, U31.A8, U31.A9, U31.B2, U31.B9, U31.B10, U31.C1, U31.C10, U31.D2, U31.D9, U31.E1, U31.E2, U31.E9, U31.E10, U31.F1, U31.F2, U31.F9, U31.G1, U31.G10, U31.H1, U31.H2, U31.H9, U31.J3, U31.J5, U31.J6, U31.J8, U31.K4, U31.K5, U31.K7, U33.15, Y11.2, Y11.4
GND11: C111.2, C112.2, C113.2, C114.1, C115.2, C116.2, C117.2, C118.2, C119.2, C120.2, J23.6, J23.9, J23.14, J23.20, J23.25, J24.2, R12.1, U34.A3, U34.A4, U34.A5, U34.A6, U34.A7, U34.A8, U34.A9, U34.B2, U34.B9, U34.B10, U34.C1, U34.C10, U34.D2, U34.D9, U34.E1, U34.E2, U34.E9, U34.E10, U34.F1, U34.F2, U34.F9, U34.G1, U34.G10, U34.H1, U34.H2, U34.H9, U34.J3, U34.J5, U34.J6, U34.J8, U34.K4, U34.K5, U34.K7, U36.15, Y12.2, Y12.4
GND12: C121.2, C122.2, C123.2, C124.1, C125.2, C126.2, C127.2, C128.2, C129.2, C130.2, J25.6, J25.9, J25.14, J25.20, J25.25, J26.2, R13.1, U37.A3, U37.A4, U37.A5, U37.A6, U37.A7, U37.A8, U37.A9, U37.B2, U37.B9, U37.B10, U37.C1, U37.C10, U37.D2, U37.D9, U37.E1, U37.E2, U37.E9, U37.E10, U37.F1, U37.F2, U37.F9, U37.G1, U37.G10, U37.H1, U37.H2, U37.H9, U37.J3, U37.J5, U37.J6, U37.J8, U37.K4, U37.K5, U37.K7, U39.15, Y13.2, Y13.4
GND13: C131.2, C132.2, C133.2, C134.1, C135.2, C136.2, C137.2, C138.2, C139.2, C140.2, J27.6, J27.9, J27.14, J27.20, J27.25, J28.2, R14.1, U40.A3, U40.A4, U40.A5, U40.A6, U40.A7, U40.A8, U40.A9, U40.B2, U40.B9, U40.B10, U40.C1, U40.C10, U40.D2, U40.D9, U40.E1, U40.E2, U40.E9, U40.E10, U40.F1, U40.F2, U40.F9, U40.G1, U40.G10, U40.H1, U40.H2, U40.H9, U40.J3, U40.J5, U40.J6, U40.J8, U40.K4, U40.K5, U40.K7, U42.15, Y14.2, Y14.4
GND14: C141.2, C142.2, C143.2, C144.1, C145.2, C146.2, C147.2, C148.2, C149.2, C150.2, J29.6, J29.9, J29.14, J29.20, J29.25, J30.2, R15.1, U43.A3, U43.A4, U43.A5, U43.A6, U43.A7, U43.A8, U43.A9, U43.B2, U43.B9, U43.B10, U43.C1, U43.C10, U43.D2, U43.D9, U43.E1, U43.E2, U43.E9, U43.E10, U43.F1, U43.F2, U43.F9, U43.G1, U43.G10, U43.H1, U43.H2, U43.H9, U43.J3, U43.J5, U43.J6, U43.J8, U43.K4, U43.K5, U43.K7, U45.15, Y15.2, Y15.4
GND15: C151.2, C152.2, C153.2, C154.1, C155.2, C156.2, C157.2, C158.2, C159.2, C160.2, J31.6, J31.9, J31.14, J31.20, J31.25, J32.2, R16.1, U46.A3, U46.A4, U46.A5, U46.A6, U46.A7, U46.A8, U46.A9, U46.B2, U46.B9, U46.B10, U46.C1, U46.C10, U46.D2, U46.D9, U46.E1, U46.E2, U46.E9, U46.E10, U46.F1, U46.F2, U46.F9, U46.G1, U46.G10, U46.H1, U46.H2, U46.H9, U46.J3, U46.J5, U46.J6, U46.J8, U46.K4, U46.K5, U46.K7, U48.15, Y16.2, Y16.4
INTERRUPT: R1.2, U1.K8, U4.9
INTERRUPT1: R2.2, U3.K8, U6.9
INTERRUPT2: R3.2, U7.K8, U9.9
INTERRUPT3: R4.2, U10.K8, U12.9
INTERRUPT4: R5.2, U13.K8, U15.9
INTERRUPT5: R6.2, U16.K8, U18.9
INTERRUPT6: R7.2, U19.K8, U21.9
INTERRUPT7: R8.2, U22.K8, U24.9
INTERRUPT8: R9.2, U25.K8, U27.9
INTERRUPT9: R10.2, U28.K8, U30.9
INTERRUPT10: R11.2, U31.K8, U33.9
INTERRUPT11: R12.2, U34.K8, U36.9
INTERRUPT12: R13.2, U37.K8, U39.9
INTERRUPT13: R14.2, U40.K8, U42.9
INTERRUPT14: R15.2, U43.K8, U45.9
INTERRUPT15: R16.2, U46.K8, U48.9
INTERRUPT_RPI: J2.4, J4.22, U4.12
INTERRUPT_RPI1: J1.22, J3.4, U6.12
INTERRUPT_RPI2: J5.22, J6.4, U9.12
INTERRUPT_RPI3: J7.22, J8.4, U12.12
INTERRUPT_RPI4: J9.22, J10.4, U15.12
INTERRUPT_RPI5: J11.22, J12.4, U18.12
INTERRUPT_RPI6: J13.22, J14.4, U21.12
INTERRUPT_RPI7: J15.22, J16.4, U24.12
INTERRUPT_RPI8: J17.22, J18.4, U27.12
INTERRUPT_RPI9: J19.22, J20.4, U30.12
INTERRUPT_RPI10: J21.22, J22.4, U33.12
INTERRUPT_RPI11: J23.22, J24.4, U36.12
INTERRUPT_RPI12: J25.22, J26.4, U39.12
INTERRUPT_RPI13: J27.22, J28.4, U42.12
INTERRUPT_RPI14: J29.22, J30.4, U45.12
INTERRUPT_RPI15: J31.22, J32.4, U48.12
MISO: U1.K3, U4.3
MISO1: U3.K3, U6.3
MISO2: U7.K3, U9.3
MISO3: U10.K3, U12.3
MISO4: U13.K3, U15.3
MISO5: U16.K3, U18.3
MISO6: U19.K3, U21.3
MISO7: U22.K3, U24.3
MISO8: U25.K3, U27.3
MISO9: U28.K3, U30.3
MISO10: U31.K3, U33.3
MISO11: U34.K3, U36.3
MISO12: U37.K3, U39.3
MISO13: U40.K3, U42.3
MISO14: U43.K3, U45.3
MISO15: U46.K3, U48.3
MISO_RPI: J2.6, J4.21, U4.18
MISO_RPI1: J1.21, J3.6, U6.18
MISO_RPI2: J5.21, J6.6, U9.18
MISO_RPI3: J7.21, J8.6, U12.18
MISO_RPI4: J9.21, J10.6, U15.18
MISO_RPI5: J11.21, J12.6, U18.18
MISO_RPI6: J13.21, J14.6, U21.18
MISO_RPI7: J15.21, J16.6, U24.18
MISO_RPI8: J17.21, J18.6, U27.18
MISO_RPI9: J19.21, J20.6, U30.18
MISO_RPI10: J21.21, J22.6, U33.18
MISO_RPI11: J23.21, J24.6, U36.18
MISO_RPI12: J25.21, J26.6, U39.18
MISO_RPI13: J27.21, J28.6, U42.18
MISO_RPI14: J29.21, J30.6, U45.18
MISO_RPI15: J31.21, J32.6, U48.18
MOSI: U1.K6, U4.8
MOSI1: U3.K6, U6.8
MOSI2: U7.K6, U9.8
MOSI3: U10.K6, U12.8
MOSI4: U13.K6, U15.8
MOSI5: U16.K6, U18.8
MOSI6: U19.K6, U21.8
MOSI7: U22.K6, U24.8
MOSI8: U25.K6, U27.8
MOSI9: U28.K6, U30.8
MOSI10: U31.K6, U33.8
MOSI11: U34.K6, U36.8
MOSI12: U37.K6, U39.8
MOSI13: U40.K6, U42.8
MOSI14: U43.K6, U45.8
MOSI15: U46.K6, U48.8
MOSI_RPI: J2.5, J4.19, U4.13
MOSI_RPI1: J1.19, J3.5, U6.13
MOSI_RPI2: J5.19, J6.5, U9.13
MOSI_RPI3: J7.19, J8.5, U12.13
MOSI_RPI4: J9.19, J10.5, U15.13
MOSI_RPI5: J11.19, J12.5, U18.13
MOSI_RPI6: J13.19, J14.5, U21.13
MOSI_RPI7: J15.19, J16.5, U24.13
MOSI_RPI8: J17.19, J18.5, U27.13
MOSI_RPI9: J19.19, J20.5, U30.13
MOSI_RPI10: J21.19, J22.5, U33.13
MOSI_RPI11: J23.19, J24.5, U36.13
MOSI_RPI12: J25.19, J26.5, U39.13
MOSI_RPI13: J27.19, J28.5, U42.13
MOSI_RPI14: J29.19, J30.5, U45.13
MOSI_RPI15: J31.19, J32.5, U48.13
unnamed: C3.1, U1.J10, Y1.1
unnamed: C4.2, U1.H10, Y1.3
unnamed: C13.1, U3.J10, Y2.1
unnamed: C14.2, U3.H10, Y2.3
unnamed: C23.1, U7.J10, Y3.1
unnamed: C24.2, U7.H10, Y3.3
unnamed: C33.1, U10.J10, Y4.1
unnamed: C34.2, U10.H10, Y4.3
unnamed: C43.1, U13.J10, Y5.1
unnamed: C44.2, U13.H10, Y5.3
unnamed: C53.1, U16.J10, Y6.1
unnamed: C54.2, U16.H10, Y6.3
unnamed: C63.1, U19.J10, Y7.1
unnamed: C64.2, U19.H10, Y7.3
unnamed: C73.1, U22.J10, Y8.1
unnamed: C74.2, U22.H10, Y8.3
unnamed: C83.1, U25.J10, Y9.1
unnamed: C84.2, U25.H10, Y9.3
unnamed: C93.1, U28.J10, Y10.1
unnamed: C94.2, U28.H10, Y10.3
unnamed: C103.1, U31.J10, Y11.1
unnamed: C104.2, U31.H10, Y11.3
unnamed: C113.1, U34.J10, Y12.1
unnamed: C114.2, U34.H10, Y12.3
unnamed: C123.1, U37.J10, Y13.1
unnamed: C124.2, U37.H10, Y13.3
unnamed: C133.1, U40.J10, Y14.1
unnamed: C134.2, U40.H10, Y14.3
unnamed: C143.1, U43.J10, Y15.1
unnamed: C144.2, U43.H10, Y15.3
unnamed: C153.1, U46.J10, Y16.1
unnamed: C154.2, U46.H10, Y16.3
SCLK: U1.K2, U4.2
SCLK1: U3.K2, U6.2
SCLK2: U7.K2, U9.2
SCLK3: U10.K2, U12.2
SCLK4: U13.K2, U15.2
SCLK5: U16.K2, U18.2
SCLK6: U19.K2, U21.2
SCLK7: U22.K2, U24.2
SCLK8: U25.K2, U27.2
SCLK9: U28.K2, U30.2
SCLK10: U31.K2, U33.2
SCLK11: U34.K2, U36.2
SCLK12: U37.K2, U39.2
SCLK13: U40.K2, U42.2
SCLK14: U43.K2, U45.2
SCLK15: U46.K2, U48.2
SCLK_RPI: J2.7, J4.23, U4.19
SCLK_RPI1: J1.23, J3.7, U6.19
SCLK_RPI2: J5.23, J6.7, U9.19
SCLK_RPI3: J7.23, J8.7, U12.19
SCLK_RPI4: J9.23, J10.7, U15.19
SCLK_RPI5: J11.23, J12.7, U18.19
SCLK_RPI6: J13.23, J14.7, U21.19
SCLK_RPI7: J15.23, J16.7, U24.19
SCLK_RPI8: J17.23, J18.7, U27.19
SCLK_RPI9: J19.23, J20.7, U30.19
SCLK_RPI10: J21.23, J22.7, U33.19
SCLK_RPI11: J23.23, J24.7, U36.19
SCLK_RPI12: J25.23, J26.7, U39.19
SCLK_RPI13: J27.23, J28.7, U42.19
SCLK_RPI14: J29.23, J30.7, U45.19
SCLK_RPI15: J31.23, J32.7, U48.19

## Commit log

2018-05-24 Initial commit of hardware layout.
2018-05-24 Adding A111 documentation.
2018-05-24 Adding 5x5 production panel.
2018-07-27 Initial commit of example distance detector, board source, and makefiles.
2018-08-02 Adding product info to the readme.
2018-10-09 Updating makefile and source to be compatible with 1.3.9
2018-11-26 Updating board source and make rules for compatibility with SDK v1.3.11
2018-12-20 Updating SparkX board source file for SDK 1.4.0
2019-02-13 Adding compiled example software binaries.
2019-03-18 Updated method signatures to match 1.7.0 board defs
2019-03-18 Updated detector_distance example for 1.7.0
2019-03-18 Renamed folders for easier integration instructions
2019-03-18 Added installation instructions

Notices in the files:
parts and their libraries:
SparkFun-Aesthetics: Licensing: Creative Commons ShareAlike 4.0 International - https://creativecommons.org/licenses/by-sa/4.0
SparkFun-Aesthetics: Released under the Creative Commons Attribution Share-Alike 4.0 License
SparkFun-Aesthetics: https://creativecommons.org/licenses/by-sa/4.0
